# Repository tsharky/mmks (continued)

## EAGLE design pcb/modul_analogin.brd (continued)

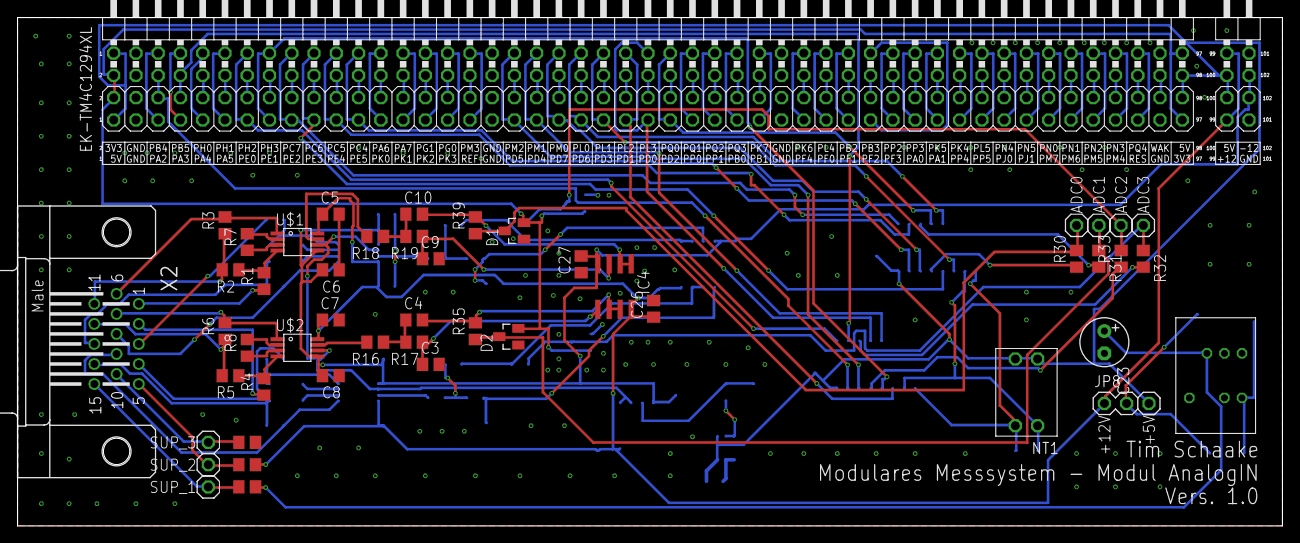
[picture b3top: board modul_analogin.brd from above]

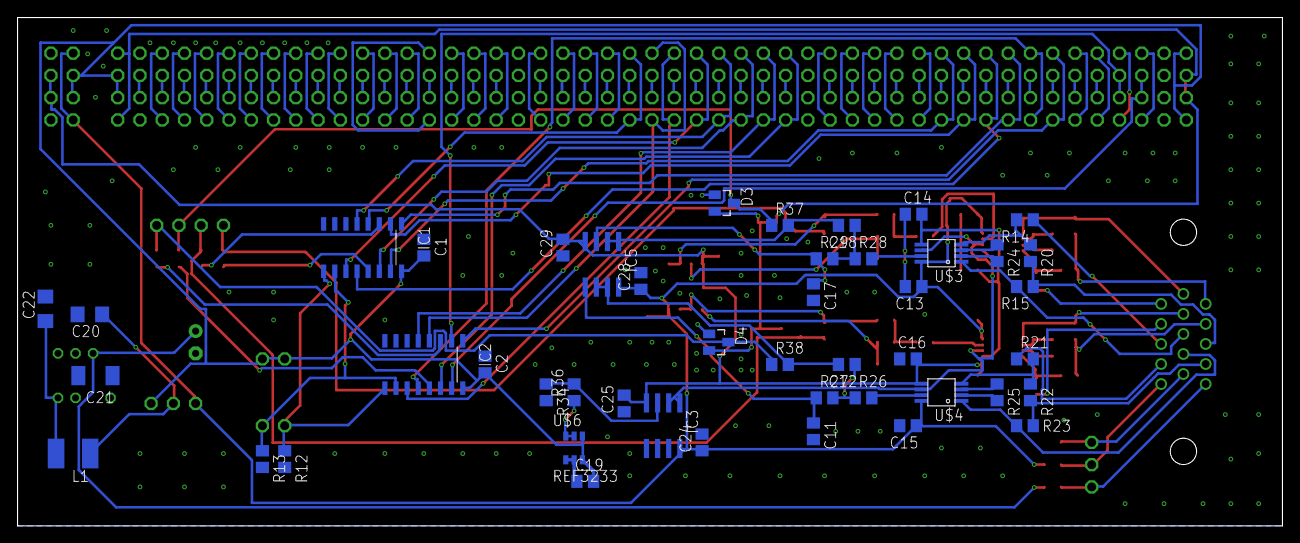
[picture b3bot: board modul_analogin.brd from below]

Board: 2 copper layers, 144.3 x 58.0 mm, 96 parts (46 on the bottom side), 153 nets.

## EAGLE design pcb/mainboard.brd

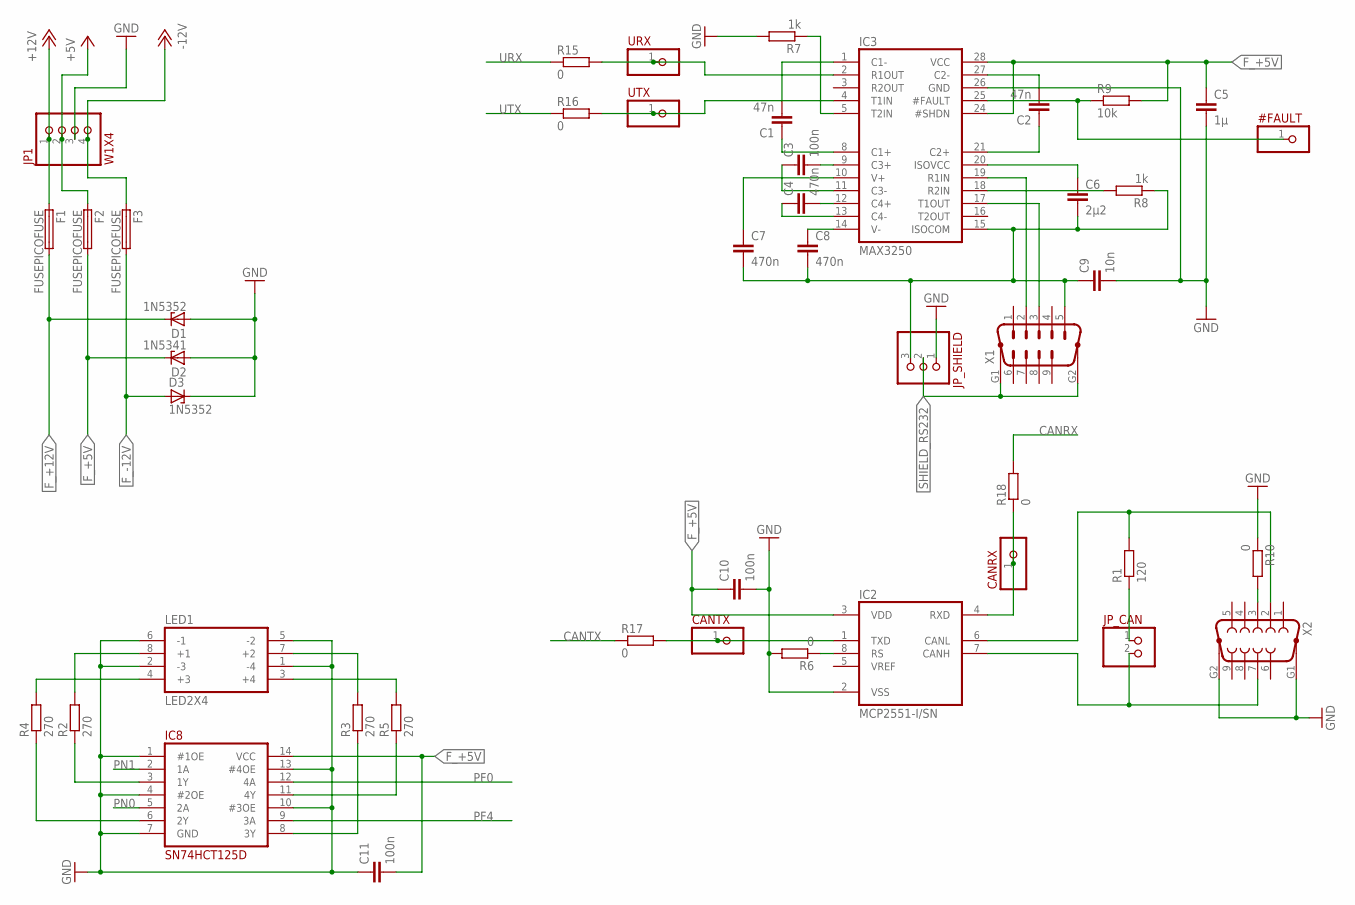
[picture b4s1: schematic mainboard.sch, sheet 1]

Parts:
#FAULT: PINH-1X1; 1X1
C1, C2: 47n; C2220
C3, C10, C11: 100n; C0805
C4, C7, C8: 470n; C0805
C5: 1µ; C0805
C6: 2µ2; C0805
C9: 10n; C1812
CANRX: PINH-1X1; 1X1
CANTX: PINH-1X1; 1X1
D1, D3: 1N5352; C1702-15
D2: 1N5341; C1702-15
F1, F2, F3: FUSEPICOFUSE; PICOFUSE
IC2: MCP2551-I/SN; SO08
IC3: MAX3250; SSOP28_A28M-3
IC8: SN74HCT125D; SOIC14_D
JP1: W1X4
JP_CAN: PINH-1X2; 1X2
JP_SHIELD: PINH-1X3; 1X3
LED1: LED2X4
R1: 120; R0805
R2, R3, R4, R5: 270; R0805
R6, R10, R15, R16, R17, R18: 0; R0805
R7, R8: 1k; R0805
R9: 10k; R0805
URX: PINH-1X1; 1X1
UTX: PINH-1X1; 1X1
X1: M09HP
X2: F09HP

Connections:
+5V: F2.1, JP1.2
+12V: F1.1, JP1.1
-12V: F3.1, JP1.4
CANRX: R18.2; also elsewhere on the board
CANTX: R17.1; also elsewhere on the board
F_+5V: C5.1, C10.1, C11.2, D2.C, F2.2, IC2.3 (VDD), IC3.24 (#SHDN), IC3.28 (VCC), IC8.14 (VCC), R9.2; also elsewhere on the board
F_+12V: D1.C, F1.2; also elsewhere on the board
F_-12V: D3.A, F3.2; also elsewhere on the board
GND: C5.2, C9.2, C10.2, C11.1, D1.A, D2.A, D3.C, IC2.2 (VSS), IC3.26 (GND), IC8.1 (#1OE), IC8.4 (#2OE), IC8.7 (GND), IC8.10 (#3OE), IC8.13 (#4OE), JP1.3, JP_SHIELD.1, LED1.1 (-4), LED1.2 (-3), LED1.5 (-2), LED1.6 (-1), R6.2, R7.2, R10.1, X2.G1, X2.G2; also elsewhere on the board
ISOCOM: C6.2, C7.2, C8.2, C9.1, IC3.15 (ISOCOM), JP_SHIELD.3, R8.1, X1.5
unnamed: JP_CAN.1, R1.1
unnamed: IC3.17 (T1OUT), X1.3
unnamed: C4.2, IC3.12 (C4+)
unnamed: C4.1, IC3.13 (C4-)
unnamed: IC3.19 (R1IN), X1.2
unnamed: C3.2, IC3.9 (C3+)
unnamed: C3.1, IC3.11 (C3-)
unnamed: C2.1, IC3.21 (C2+)
unnamed: C2.2, IC3.27 (C2-)
unnamed: C1.2, IC3.1 (C1-)
unnamed: C1.1, IC3.8 (C1+)
unnamed: C6.1, IC3.20 (ISOVCC)
unnamed: IC3.2 (R1OUT), R15.2, URX.1
unnamed: IC3.4 (T1IN), R16.2, UTX.1
unnamed: CANTX.1, IC2.1 (TXD), R17.2
unnamed: CANRX.1, IC2.4 (RXD), R18.1
unnamed: IC2.8 (RS), R6.1
unnamed: LED1.7 (+2), R3.2
unnamed: IC8.3 (1Y), R2.1
unnamed: IC8.6 (2Y), R4.1
unnamed: IC8.8 (3Y), R3.1
unnamed: IC8.11 (4Y), R5.1
unnamed: LED1.3 (+4), R5.2
unnamed: LED1.8 (+1), R2.2
unnamed: LED1.4 (+3), R4.2
unnamed: IC3.18 (R2IN), R8.2
unnamed: IC3.5 (T2IN), R7.1
unnamed: #FAULT.1, IC3.25 (#FAULT), R9.1
unnamed: R10.2, X2.3
unnamed: IC2.7 (CANH), JP_CAN.2, X2.7
unnamed: IC2.6 (CANL), R1.2, X2.2
PF0: IC8.12 (4A); also elsewhere on the board
PF4: IC8.9 (3A); also elsewhere on the board
PN0: IC8.5 (2A); also elsewhere on the board
PN1: IC8.2 (1A); also elsewhere on the board
SHIELD_RS232: JP_SHIELD.2, X1.G1, X1.G2
URX: R15.1; also elsewhere on the board
UTX: R16.1; also elsewhere on the board
V+: C7.1, IC3.10 (V+)
V-: C8.1, IC3.14 (V-)

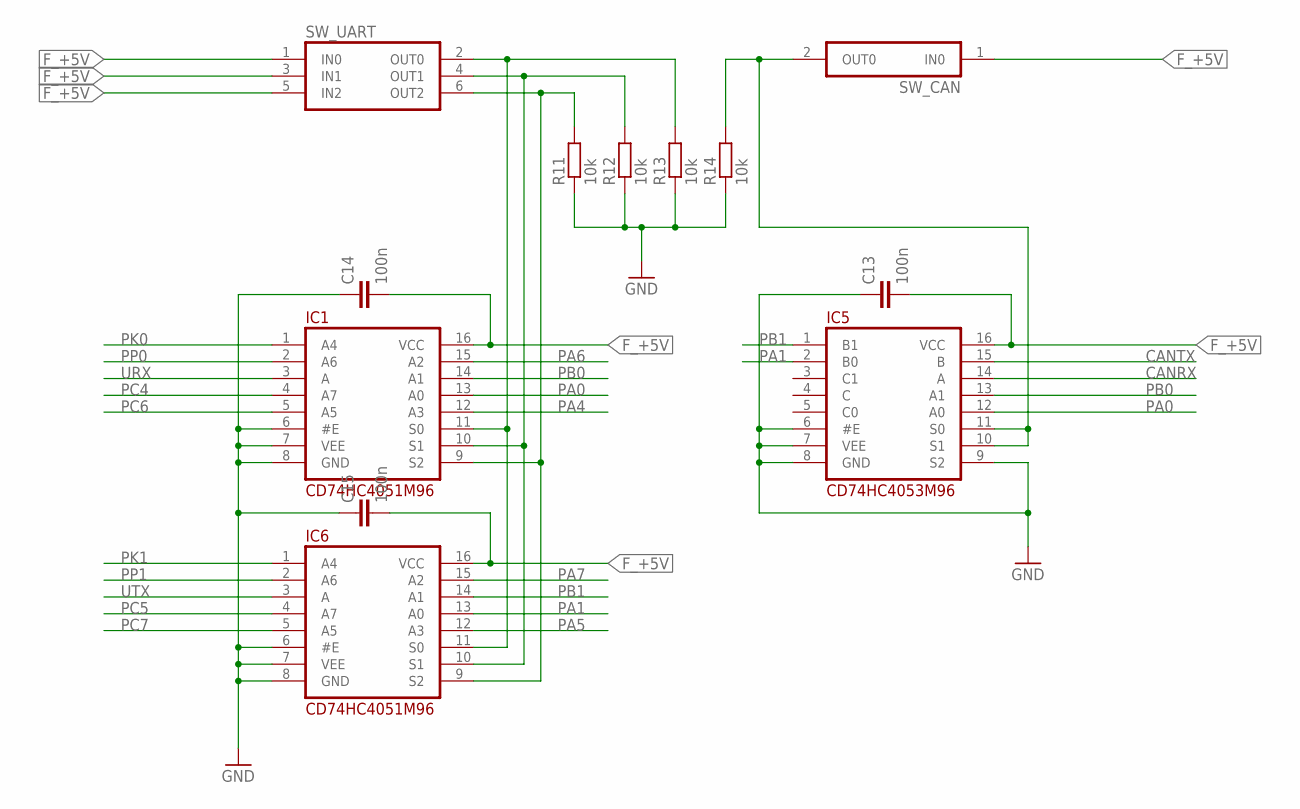
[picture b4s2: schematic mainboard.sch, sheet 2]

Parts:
C13, C14, C15: 100n; C0805
IC1, IC6: CD74HC4051M96; SOIC16_D
IC5: CD74HC4053M96; SOIC16_D
R11, R12, R13, R14: 10k; R0805
SW_CAN: NT01
SW_UART: NT03

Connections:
CANRX: IC5.14 (A); also elsewhere on the board
CANTX: IC5.15 (B); also elsewhere on the board
F_+5V: C13.2, C14.2, C15.2, IC1.16 (VCC), IC5.16 (VCC), IC6.16 (VCC), SW_CAN.1 (IN0), SW_UART.1 (IN0), SW_UART.3 (IN1), SW_UART.5 (IN2); also elsewhere on the board
GND: C13.1, C14.1, C15.1, IC1.6 (#E), IC1.7 (VEE), IC1.8 (GND), IC5.6 (#E), IC5.7 (VEE), IC5.8 (GND), IC5.9 (S2), IC6.6 (#E), IC6.7 (VEE), IC6.8 (GND), R11.1, R12.1, R13.1, R14.1; also elsewhere on the board
unnamed: IC1.9 (S2), IC6.9 (S2), R11.2, SW_UART.6 (OUT2)
unnamed: IC1.10 (S1), IC6.10 (S1), R12.2, SW_UART.4 (OUT1)
unnamed: IC1.11 (S0), IC6.11 (S0), R13.2, SW_UART.2 (OUT0)
unnamed: IC5.10 (S1), IC5.11 (S0), R14.2, SW_CAN.2 (OUT0)
PA0: IC1.13 (A0), IC5.12 (A0); also elsewhere on the board
PA1: IC5.2 (B0), IC6.13 (A0); also elsewhere on the board
PA4: IC1.12 (A3); also elsewhere on the board
PA5: IC6.12 (A3); also elsewhere on the board
PA6: IC1.15 (A2); also elsewhere on the board
PA7: IC6.15 (A2); also elsewhere on the board
PB0: IC1.14 (A1), IC5.13 (A1); also elsewhere on the board
PB1: IC5.1 (B1), IC6.14 (A1); also elsewhere on the board
PC4: IC1.4 (A7); also elsewhere on the board
PC5: IC6.4 (A7); also elsewhere on the board
PC6: IC1.5 (A5); also elsewhere on the board
PC7: IC6.5 (A5); also elsewhere on the board
PK0: IC1.1 (A4); also elsewhere on the board
PK1: IC6.1 (A4); also elsewhere on the board
PP0: IC1.2 (A6); also elsewhere on the board
PP1: IC6.2 (A6); also elsewhere on the board
URX: IC1.3 (A); also elsewhere on the board
UTX: IC6.3 (A); also elsewhere on the board

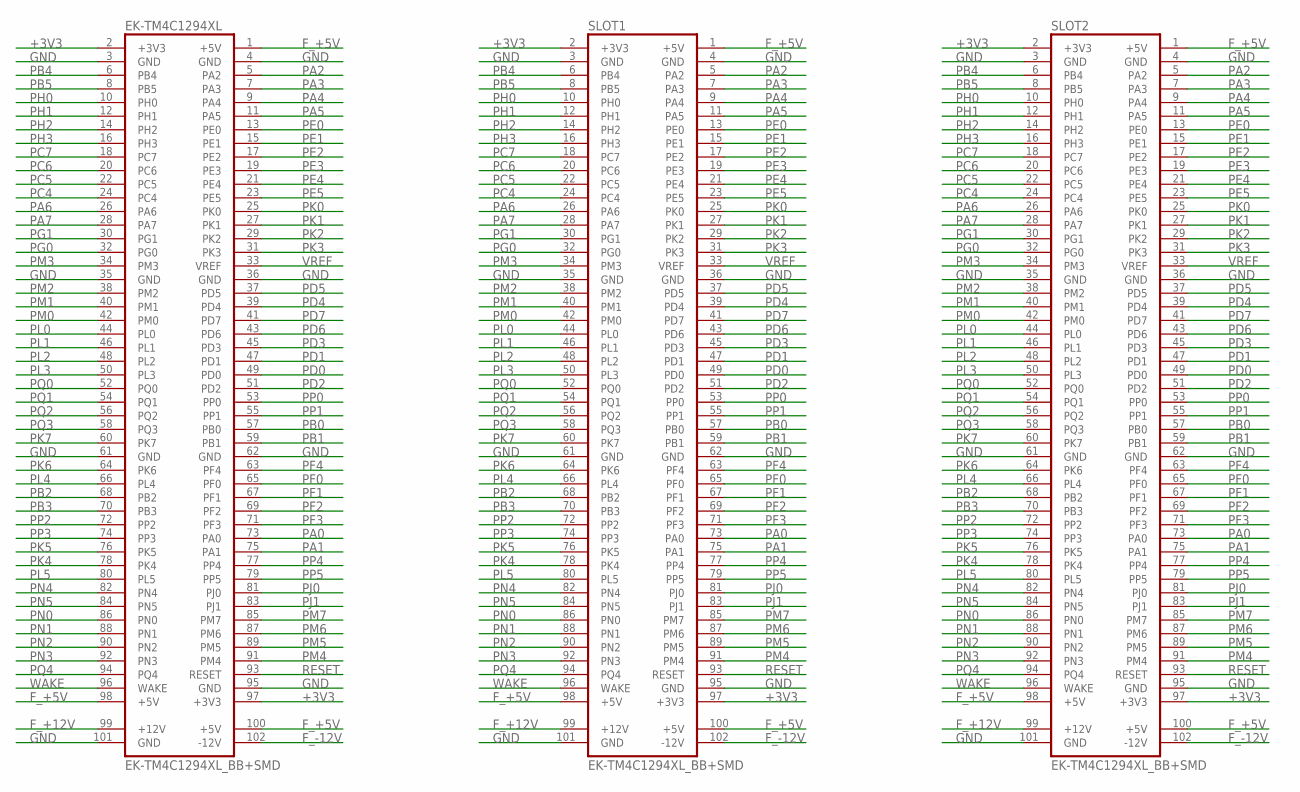
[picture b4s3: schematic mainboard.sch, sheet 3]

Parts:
EK-TM4C1294XL: EK-TM4C1294XL_BB+SMD
SLOT1, SLOT2: EK-TM4C1294XL_BB+SMD

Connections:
+3V3: EK-TM4C1294XL.2 (+3V3), EK-TM4C1294XL.97 (+3V3), SLOT1.2 (+3V3), SLOT1.97 (+3V3), SLOT2.2 (+3V3), SLOT2.97 (+3V3); also elsewhere on the board
F_+5V: EK-TM4C1294XL.1 (+5V), EK-TM4C1294XL.98 (+5V), EK-TM4C1294XL.100 (+5V), SLOT1.1 (+5V), SLOT1.98 (+5V), SLOT1.100 (+5V), SLOT2.1 (+5V), SLOT2.98 (+5V), SLOT2.100 (+5V); also elsewhere on the board
F_+12V: EK-TM4C1294XL.99 (+12V), SLOT1.99 (+12V), SLOT2.99 (+12V); also elsewhere on the board
F_-12V: EK-TM4C1294XL.102 (-12V), SLOT1.102 (-12V), SLOT2.102 (-12V); also elsewhere on the board
GND: EK-TM4C1294XL.3 (GND), EK-TM4C1294XL.4 (GND), EK-TM4C1294XL.35 (GND), EK-TM4C1294XL.36 (GND), EK-TM4C1294XL.61 (GND), EK-TM4C1294XL.62 (GND), EK-TM4C1294XL.95 (GND), EK-TM4C1294XL.101 (GND), SLOT1.3 (GND), SLOT1.4 (GND), SLOT1.35 (GND), SLOT1.36 (GND), SLOT1.61 (GND), SLOT1.62 (GND), SLOT1.95 (GND), SLOT1.101 (GND), SLOT2.3 (GND), SLOT2.4 (GND), SLOT2.35 (GND), SLOT2.36 (GND), SLOT2.61 (GND), SLOT2.62 (GND), SLOT2.95 (GND), SLOT2.101 (GND); also elsewhere on the board
PA0: EK-TM4C1294XL.73 (PA0), SLOT1.73 (PA0), SLOT2.73 (PA0); also elsewhere on the board
PA1: EK-TM4C1294XL.75 (PA1), SLOT1.75 (PA1), SLOT2.75 (PA1); also elsewhere on the board
PA2: EK-TM4C1294XL.5 (PA2), SLOT1.5 (PA2), SLOT2.5 (PA2); also elsewhere on the board
PA3: EK-TM4C1294XL.7 (PA3), SLOT1.7 (PA3), SLOT2.7 (PA3); also elsewhere on the board
PA4: EK-TM4C1294XL.9 (PA4), SLOT1.9 (PA4), SLOT2.9 (PA4); also elsewhere on the board
PA5: EK-TM4C1294XL.11 (PA5), SLOT1.11 (PA5), SLOT2.11 (PA5); also elsewhere on the board
PA6: EK-TM4C1294XL.26 (PA6), SLOT1.26 (PA6), SLOT2.26 (PA6); also elsewhere on the board
PA7: EK-TM4C1294XL.28 (PA7), SLOT1.28 (PA7), SLOT2.28 (PA7); also elsewhere on the board
PB0: EK-TM4C1294XL.57 (PB0), SLOT1.57 (PB0), SLOT2.57 (PB0); also elsewhere on the board
PB1: EK-TM4C1294XL.59 (PB1), SLOT1.59 (PB1), SLOT2.59 (PB1); also elsewhere on the board
PB2: EK-TM4C1294XL.68 (PB2), SLOT1.68 (PB2), SLOT2.68 (PB2); also elsewhere on the board
PB3: EK-TM4C1294XL.70 (PB3), SLOT1.70 (PB3), SLOT2.70 (PB3); also elsewhere on the board
PB4: EK-TM4C1294XL.6 (PB4), SLOT1.6 (PB4), SLOT2.6 (PB4); also elsewhere on the board
PB5: EK-TM4C1294XL.8 (PB5), SLOT1.8 (PB5), SLOT2.8 (PB5); also elsewhere on the board
PC4: EK-TM4C1294XL.24 (PC4), SLOT1.24 (PC4), SLOT2.24 (PC4); also elsewhere on the board
PC5: EK-TM4C1294XL.22 (PC5), SLOT1.22 (PC5), SLOT2.22 (PC5); also elsewhere on the board
PC6: EK-TM4C1294XL.20 (PC6), SLOT1.20 (PC6), SLOT2.20 (PC6); also elsewhere on the board
PC7: EK-TM4C1294XL.18 (PC7), SLOT1.18 (PC7), SLOT2.18 (PC7); also elsewhere on the board
PD0: EK-TM4C1294XL.49 (PD0), SLOT1.49 (PD0), SLOT2.49 (PD0); also elsewhere on the board
PD1: EK-TM4C1294XL.47 (PD1), SLOT1.47 (PD1), SLOT2.47 (PD1); also elsewhere on the board
PD2: EK-TM4C1294XL.51 (PD2), SLOT1.51 (PD2), SLOT2.51 (PD2); also elsewhere on the board
PD3: EK-TM4C1294XL.45 (PD3), SLOT1.45 (PD3), SLOT2.45 (PD3); also elsewhere on the board
PD4: EK-TM4C1294XL.39 (PD4), SLOT1.39 (PD4), SLOT2.39 (PD4); also elsewhere on the board
PD5: EK-TM4C1294XL.37 (PD5), SLOT1.37 (PD5), SLOT2.37 (PD5); also elsewhere on the board
PD6: EK-TM4C1294XL.43 (PD6), SLOT1.43 (PD6), SLOT2.43 (PD6); also elsewhere on the board
PD7: EK-TM4C1294XL.41 (PD7), SLOT1.41 (PD7), SLOT2.41 (PD7); also elsewhere on the board
PE0: EK-TM4C1294XL.13 (PE0), SLOT1.13 (PE0), SLOT2.13 (PE0); also elsewhere on the board
PE1: EK-TM4C1294XL.15 (PE1), SLOT1.15 (PE1), SLOT2.15 (PE1); also elsewhere on the board
PE2: EK-TM4C1294XL.17 (PE2), SLOT1.17 (PE2), SLOT2.17 (PE2); also elsewhere on the board
PE3: EK-TM4C1294XL.19 (PE3), SLOT1.19 (PE3), SLOT2.19 (PE3); also elsewhere on the board
PE4: EK-TM4C1294XL.21 (PE4), SLOT1.21 (PE4), SLOT2.21 (PE4); also elsewhere on the board
PE5: EK-TM4C1294XL.23 (PE5), SLOT1.23 (PE5), SLOT2.23 (PE5); also elsewhere on the board
PF0: EK-TM4C1294XL.65 (PF0), SLOT1.65 (PF0), SLOT2.65 (PF0); also elsewhere on the board
PF1: EK-TM4C1294XL.67 (PF1), SLOT1.67 (PF1), SLOT2.67 (PF1); also elsewhere on the board
PF2: EK-TM4C1294XL.69 (PF2), SLOT1.69 (PF2), SLOT2.69 (PF2); also elsewhere on the board
PF3: EK-TM4C1294XL.71 (PF3), SLOT1.71 (PF3), SLOT2.71 (PF3); also elsewhere on the board
PF4: EK-TM4C1294XL.63 (PF4), SLOT1.63 (PF4), SLOT2.63 (PF4); also elsewhere on the board
PG0: EK-TM4C1294XL.32 (PG0), SLOT1.32 (PG0), SLOT2.32 (PG0); also elsewhere on the board
PG1: EK-TM4C1294XL.30 (PG1), SLOT1.30 (PG1), SLOT2.30 (PG1); also elsewhere on the board
PH0: EK-TM4C1294XL.10 (PH0), SLOT1.10 (PH0), SLOT2.10 (PH0); also elsewhere on the board
PH1: EK-TM4C1294XL.12 (PH1), SLOT1.12 (PH1), SLOT2.12 (PH1); also elsewhere on the board
PH2: EK-TM4C1294XL.14 (PH2), SLOT1.14 (PH2), SLOT2.14 (PH2); also elsewhere on the board
PH3: EK-TM4C1294XL.16 (PH3), SLOT1.16 (PH3), SLOT2.16 (PH3); also elsewhere on the board
PJ0: EK-TM4C1294XL.81 (PJ0), SLOT1.81 (PJ0), SLOT2.81 (PJ0); also elsewhere on the board
PJ1: EK-TM4C1294XL.83 (PJ1), SLOT1.83 (PJ1), SLOT2.83 (PJ1); also elsewhere on the board
PK0: EK-TM4C1294XL.25 (PK0), SLOT1.25 (PK0), SLOT2.25 (PK0); also elsewhere on the board
PK1: EK-TM4C1294XL.27 (PK1), SLOT1.27 (PK1), SLOT2.27 (PK1); also elsewhere on the board
PK2: EK-TM4C1294XL.29 (PK2), SLOT1.29 (PK2), SLOT2.29 (PK2); also elsewhere on the board
PK3: EK-TM4C1294XL.31 (PK3), SLOT1.31 (PK3), SLOT2.31 (PK3); also elsewhere on the board
PK4: EK-TM4C1294XL.78 (PK4), SLOT1.78 (PK4), SLOT2.78 (PK4); also elsewhere on the board
PK5: EK-TM4C1294XL.76 (PK5), SLOT1.76 (PK5), SLOT2.76 (PK5); also elsewhere on the board
PK6: EK-TM4C1294XL.64 (PK6), SLOT1.64 (PK6), SLOT2.64 (PK6); also elsewhere on the board
PK7: EK-TM4C1294XL.60 (PK7), SLOT1.60 (PK7), SLOT2.60 (PK7); also elsewhere on the board
PL0: EK-TM4C1294XL.44 (PL0), SLOT1.44 (PL0), SLOT2.44 (PL0); also elsewhere on the board
PL1: EK-TM4C1294XL.46 (PL1), SLOT1.46 (PL1), SLOT2.46 (PL1); also elsewhere on the board
PL2: EK-TM4C1294XL.48 (PL2), SLOT1.48 (PL2), SLOT2.48 (PL2); also elsewhere on the board
PL3: EK-TM4C1294XL.50 (PL3), SLOT1.50 (PL3), SLOT2.50 (PL3); also elsewhere on the board
PL4: EK-TM4C1294XL.66 (PL4), SLOT1.66 (PL4), SLOT2.66 (PL4); also elsewhere on the board
PL5: EK-TM4C1294XL.80 (PL5), SLOT1.80 (PL5), SLOT2.80 (PL5); also elsewhere on the board
PM0: EK-TM4C1294XL.42 (PM0), SLOT1.42 (PM0), SLOT2.42 (PM0); also elsewhere on the board
PM1: EK-TM4C1294XL.40 (PM1), SLOT1.40 (PM1), SLOT2.40 (PM1); also elsewhere on the board
PM2: EK-TM4C1294XL.38 (PM2), SLOT1.38 (PM2), SLOT2.38 (PM2); also elsewhere on the board
PM3: EK-TM4C1294XL.34 (PM3), SLOT1.34 (PM3), SLOT2.34 (PM3); also elsewhere on the board
PM4: EK-TM4C1294XL.91 (PM4), SLOT1.91 (PM4), SLOT2.91 (PM4); also elsewhere on the board
PM5: EK-TM4C1294XL.89 (PM5), SLOT1.89 (PM5), SLOT2.89 (PM5); also elsewhere on the board
PM6: EK-TM4C1294XL.87 (PM6), SLOT1.87 (PM6), SLOT2.87 (PM6); also elsewhere on the board
PM7: EK-TM4C1294XL.85 (PM7), SLOT1.85 (PM7), SLOT2.85 (PM7); also elsewhere on the board
PN0: EK-TM4C1294XL.86 (PN0), SLOT1.86 (PN0), SLOT2.86 (PN0); also elsewhere on the board
PN1: EK-TM4C1294XL.88 (PN1), SLOT1.88 (PN1), SLOT2.88 (PN1); also elsewhere on the board
PN2: EK-TM4C1294XL.90 (PN2), SLOT1.90 (PN2), SLOT2.90 (PN2); also elsewhere on the board
PN3: EK-TM4C1294XL.92 (PN3), SLOT1.92 (PN3), SLOT2.92 (PN3); also elsewhere on the board
PN4: EK-TM4C1294XL.82 (PN4), SLOT1.82 (PN4), SLOT2.82 (PN4); also elsewhere on the board
PN5: EK-TM4C1294XL.84 (PN5), SLOT1.84 (PN5), SLOT2.84 (PN5); also elsewhere on the board
PP0: EK-TM4C1294XL.53 (PP0), SLOT1.53 (PP0), SLOT2.53 (PP0); also elsewhere on the board
PP1: EK-TM4C1294XL.55 (PP1), SLOT1.55 (PP1), SLOT2.55 (PP1); also elsewhere on the board
PP2: EK-TM4C1294XL.72 (PP2), SLOT1.72 (PP2), SLOT2.72 (PP2); also elsewhere on the board
PP3: EK-TM4C1294XL.74 (PP3), SLOT1.74 (PP3), SLOT2.74 (PP3); also elsewhere on the board
PP4: EK-TM4C1294XL.77 (PP4), SLOT1.77 (PP4), SLOT2.77 (PP4); also elsewhere on the board
PP5: EK-TM4C1294XL.79 (PP5), SLOT1.79 (PP5), SLOT2.79 (PP5); also elsewhere on the board
PQ0: EK-TM4C1294XL.52 (PQ0), SLOT1.52 (PQ0), SLOT2.52 (PQ0); also elsewhere on the board
PQ1: EK-TM4C1294XL.54 (PQ1), SLOT1.54 (PQ1), SLOT2.54 (PQ1); also elsewhere on the board
PQ2: EK-TM4C1294XL.56 (PQ2), SLOT1.56 (PQ2), SLOT2.56 (PQ2); also elsewhere on the board
PQ3: EK-TM4C1294XL.58 (PQ3), SLOT1.58 (PQ3), SLOT2.58 (PQ3); also elsewhere on the board
PQ4: EK-TM4C1294XL.94 (PQ4), SLOT1.94 (PQ4), SLOT2.94 (PQ4); also elsewhere on the board
RESET: EK-TM4C1294XL.93 (RESET), SLOT1.93 (RESET), SLOT2.93 (RESET); also elsewhere on the board
VREF: EK-TM4C1294XL.33 (VREF), SLOT1.33 (VREF), SLOT2.33 (VREF); also elsewhere on the board
WAKE: EK-TM4C1294XL.96 (WAKE), SLOT1.96 (WAKE), SLOT2.96 (WAKE); also elsewhere on the board

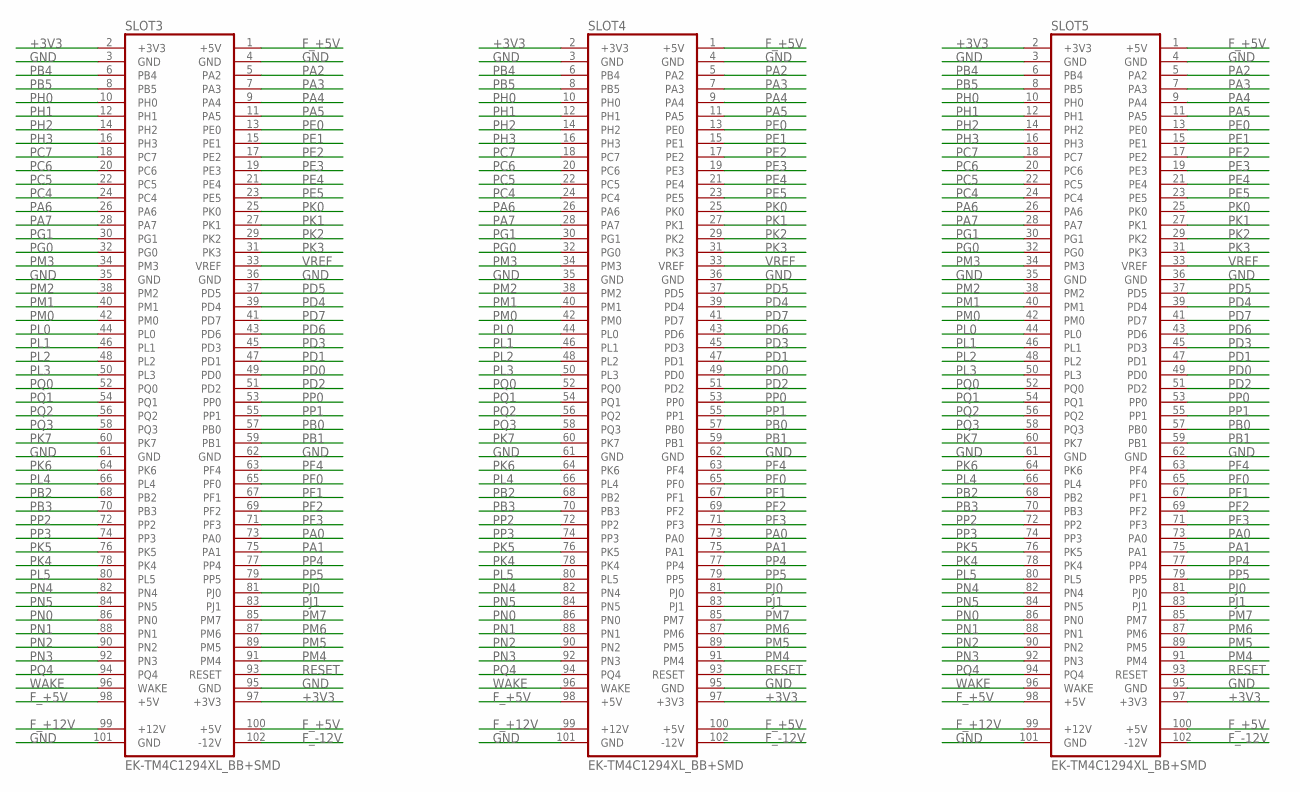
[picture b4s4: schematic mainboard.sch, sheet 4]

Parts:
SLOT3, SLOT4, SLOT5: EK-TM4C1294XL_BB+SMD

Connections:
+3V3: SLOT3.2 (+3V3), SLOT3.97 (+3V3), SLOT4.2 (+3V3), SLOT4.97 (+3V3), SLOT5.2 (+3V3), SLOT5.97 (+3V3); also elsewhere on the board
F_+5V: SLOT3.1 (+5V), SLOT3.98 (+5V), SLOT3.100 (+5V), SLOT4.1 (+5V), SLOT4.98 (+5V), SLOT4.100 (+5V), SLOT5.1 (+5V), SLOT5.98 (+5V), SLOT5.100 (+5V); also elsewhere on the board
F_+12V: SLOT3.99 (+12V), SLOT4.99 (+12V), SLOT5.99 (+12V); also elsewhere on the board
F_-12V: SLOT3.102 (-12V), SLOT4.102 (-12V), SLOT5.102 (-12V); also elsewhere on the board
GND: SLOT3.3 (GND), SLOT3.4 (GND), SLOT3.35 (GND), SLOT3.36 (GND), SLOT3.61 (GND), SLOT3.62 (GND), SLOT3.95 (GND), SLOT3.101 (GND), SLOT4.3 (GND), SLOT4.4 (GND), SLOT4.35 (GND), SLOT4.36 (GND), SLOT4.61 (GND), SLOT4.62 (GND), SLOT4.95 (GND), SLOT4.101 (GND), SLOT5.3 (GND), SLOT5.4 (GND), SLOT5.35 (GND), SLOT5.36 (GND), SLOT5.61 (GND), SLOT5.62 (GND), SLOT5.95 (GND), SLOT5.101 (GND); also elsewhere on the board
PA0: SLOT3.73 (PA0), SLOT4.73 (PA0), SLOT5.73 (PA0); also elsewhere on the board
PA1: SLOT3.75 (PA1), SLOT4.75 (PA1), SLOT5.75 (PA1); also elsewhere on the board
PA2: SLOT3.5 (PA2), SLOT4.5 (PA2), SLOT5.5 (PA2); also elsewhere on the board
PA3: SLOT3.7 (PA3), SLOT4.7 (PA3), SLOT5.7 (PA3); also elsewhere on the board
PA4: SLOT3.9 (PA4), SLOT4.9 (PA4), SLOT5.9 (PA4); also elsewhere on the board
PA5: SLOT3.11 (PA5), SLOT4.11 (PA5), SLOT5.11 (PA5); also elsewhere on the board
PA6: SLOT3.26 (PA6), SLOT4.26 (PA6), SLOT5.26 (PA6); also elsewhere on the board
PA7: SLOT3.28 (PA7), SLOT4.28 (PA7), SLOT5.28 (PA7); also elsewhere on the board
PB0: SLOT3.57 (PB0), SLOT4.57 (PB0), SLOT5.57 (PB0); also elsewhere on the board
PB1: SLOT3.59 (PB1), SLOT4.59 (PB1), SLOT5.59 (PB1); also elsewhere on the board
PB2: SLOT3.68 (PB2), SLOT4.68 (PB2), SLOT5.68 (PB2); also elsewhere on the board
PB3: SLOT3.70 (PB3), SLOT4.70 (PB3), SLOT5.70 (PB3); also elsewhere on the board
PB4: SLOT3.6 (PB4), SLOT4.6 (PB4), SLOT5.6 (PB4); also elsewhere on the board
PB5: SLOT3.8 (PB5), SLOT4.8 (PB5), SLOT5.8 (PB5); also elsewhere on the board
PC4: SLOT3.24 (PC4), SLOT4.24 (PC4), SLOT5.24 (PC4); also elsewhere on the board
PC5: SLOT3.22 (PC5), SLOT4.22 (PC5), SLOT5.22 (PC5); also elsewhere on the board
PC6: SLOT3.20 (PC6), SLOT4.20 (PC6), SLOT5.20 (PC6); also elsewhere on the board
PC7: SLOT3.18 (PC7), SLOT4.18 (PC7), SLOT5.18 (PC7); also elsewhere on the board
PD0: SLOT3.49 (PD0), SLOT4.49 (PD0), SLOT5.49 (PD0); also elsewhere on the board
PD1: SLOT3.47 (PD1), SLOT4.47 (PD1), SLOT5.47 (PD1); also elsewhere on the board
PD2: SLOT3.51 (PD2), SLOT4.51 (PD2), SLOT5.51 (PD2); also elsewhere on the board
PD3: SLOT3.45 (PD3), SLOT4.45 (PD3), SLOT5.45 (PD3); also elsewhere on the board
PD4: SLOT3.39 (PD4), SLOT4.39 (PD4), SLOT5.39 (PD4); also elsewhere on the board
PD5: SLOT3.37 (PD5), SLOT4.37 (PD5), SLOT5.37 (PD5); also elsewhere on the board
PD6: SLOT3.43 (PD6), SLOT4.43 (PD6), SLOT5.43 (PD6); also elsewhere on the board
PD7: SLOT3.41 (PD7), SLOT4.41 (PD7), SLOT5.41 (PD7); also elsewhere on the board
PE0: SLOT3.13 (PE0), SLOT4.13 (PE0), SLOT5.13 (PE0); also elsewhere on the board
PE1: SLOT3.15 (PE1), SLOT4.15 (PE1), SLOT5.15 (PE1); also elsewhere on the board
PE2: SLOT3.17 (PE2), SLOT4.17 (PE2), SLOT5.17 (PE2); also elsewhere on the board
PE3: SLOT3.19 (PE3), SLOT4.19 (PE3), SLOT5.19 (PE3); also elsewhere on the board
PE4: SLOT3.21 (PE4), SLOT4.21 (PE4), SLOT5.21 (PE4); also elsewhere on the board
PE5: SLOT3.23 (PE5), SLOT4.23 (PE5), SLOT5.23 (PE5); also elsewhere on the board
PF0: SLOT3.65 (PF0), SLOT4.65 (PF0), SLOT5.65 (PF0); also elsewhere on the board
PF1: SLOT3.67 (PF1), SLOT4.67 (PF1), SLOT5.67 (PF1); also elsewhere on the board
PF2: SLOT3.69 (PF2), SLOT4.69 (PF2), SLOT5.69 (PF2); also elsewhere on the board
PF3: SLOT3.71 (PF3), SLOT4.71 (PF3), SLOT5.71 (PF3); also elsewhere on the board
PF4: SLOT3.63 (PF4), SLOT4.63 (PF4), SLOT5.63 (PF4); also elsewhere on the board
PG0: SLOT3.32 (PG0), SLOT4.32 (PG0), SLOT5.32 (PG0); also elsewhere on the board
PG1: SLOT3.30 (PG1), SLOT4.30 (PG1), SLOT5.30 (PG1); also elsewhere on the board
PH0: SLOT3.10 (PH0), SLOT4.10 (PH0), SLOT5.10 (PH0); also elsewhere on the board
PH1: SLOT3.12 (PH1), SLOT4.12 (PH1), SLOT5.12 (PH1); also elsewhere on the board
PH2: SLOT3.14 (PH2), SLOT4.14 (PH2), SLOT5.14 (PH2); also elsewhere on the board
PH3: SLOT3.16 (PH3), SLOT4.16 (PH3), SLOT5.16 (PH3); also elsewhere on the board
PJ0: SLOT3.81 (PJ0), SLOT4.81 (PJ0), SLOT5.81 (PJ0); also elsewhere on the board
PJ1: SLOT3.83 (PJ1), SLOT4.83 (PJ1), SLOT5.83 (PJ1); also elsewhere on the board
PK0: SLOT3.25 (PK0), SLOT4.25 (PK0), SLOT5.25 (PK0); also elsewhere on the board
PK1: SLOT3.27 (PK1), SLOT4.27 (PK1), SLOT5.27 (PK1); also elsewhere on the board
PK2: SLOT3.29 (PK2), SLOT4.29 (PK2), SLOT5.29 (PK2); also elsewhere on the board
PK3: SLOT3.31 (PK3), SLOT4.31 (PK3), SLOT5.31 (PK3); also elsewhere on the board
PK4: SLOT3.78 (PK4), SLOT4.78 (PK4), SLOT5.78 (PK4); also elsewhere on the board
PK5: SLOT3.76 (PK5), SLOT4.76 (PK5), SLOT5.76 (PK5); also elsewhere on the board
PK6: SLOT3.64 (PK6), SLOT4.64 (PK6), SLOT5.64 (PK6); also elsewhere on the board
PK7: SLOT3.60 (PK7), SLOT4.60 (PK7), SLOT5.60 (PK7); also elsewhere on the board
PL0: SLOT3.44 (PL0), SLOT4.44 (PL0), SLOT5.44 (PL0); also elsewhere on the board
PL1: SLOT3.46 (PL1), SLOT4.46 (PL1), SLOT5.46 (PL1); also elsewhere on the board
PL2: SLOT3.48 (PL2), SLOT4.48 (PL2), SLOT5.48 (PL2); also elsewhere on the board
PL3: SLOT3.50 (PL3), SLOT4.50 (PL3), SLOT5.50 (PL3); also elsewhere on the board
PL4: SLOT3.66 (PL4), SLOT4.66 (PL4), SLOT5.66 (PL4); also elsewhere on the board
PL5: SLOT3.80 (PL5), SLOT4.80 (PL5), SLOT5.80 (PL5); also elsewhere on the board
PM0: SLOT3.42 (PM0), SLOT4.42 (PM0), SLOT5.42 (PM0); also elsewhere on the board
PM1: SLOT3.40 (PM1), SLOT4.40 (PM1), SLOT5.40 (PM1); also elsewhere on the board
PM2: SLOT3.38 (PM2), SLOT4.38 (PM2), SLOT5.38 (PM2); also elsewhere on the board
PM3: SLOT3.34 (PM3), SLOT4.34 (PM3), SLOT5.34 (PM3); also elsewhere on the board
PM4: SLOT3.91 (PM4), SLOT4.91 (PM4), SLOT5.91 (PM4); also elsewhere on the board
PM5: SLOT3.89 (PM5), SLOT4.89 (PM5), SLOT5.89 (PM5); also elsewhere on the board
PM6: SLOT3.87 (PM6), SLOT4.87 (PM6), SLOT5.87 (PM6); also elsewhere on the board
PM7: SLOT3.85 (PM7), SLOT4.85 (PM7), SLOT5.85 (PM7); also elsewhere on the board
PN0: SLOT3.86 (PN0), SLOT4.86 (PN0), SLOT5.86 (PN0); also elsewhere on the board
PN1: SLOT3.88 (PN1), SLOT4.88 (PN1), SLOT5.88 (PN1); also elsewhere on the board
PN2: SLOT3.90 (PN2), SLOT4.90 (PN2), SLOT5.90 (PN2); also elsewhere on the board
PN3: SLOT3.92 (PN3), SLOT4.92 (PN3), SLOT5.92 (PN3); also elsewhere on the board
PN4: SLOT3.82 (PN4), SLOT4.82 (PN4), SLOT5.82 (PN4); also elsewhere on the board
PN5: SLOT3.84 (PN5), SLOT4.84 (PN5), SLOT5.84 (PN5); also elsewhere on the board
PP0: SLOT3.53 (PP0), SLOT4.53 (PP0), SLOT5.53 (PP0); also elsewhere on the board
PP1: SLOT3.55 (PP1), SLOT4.55 (PP1), SLOT5.55 (PP1); also elsewhere on the board
PP2: SLOT3.72 (PP2), SLOT4.72 (PP2), SLOT5.72 (PP2); also elsewhere on the board
PP3: SLOT3.74 (PP3), SLOT4.74 (PP3), SLOT5.74 (PP3); also elsewhere on the board
PP4: SLOT3.77 (PP4), SLOT4.77 (PP4), SLOT5.77 (PP4); also elsewhere on the board
PP5: SLOT3.79 (PP5), SLOT4.79 (PP5), SLOT5.79 (PP5); also elsewhere on the board
PQ0: SLOT3.52 (PQ0), SLOT4.52 (PQ0), SLOT5.52 (PQ0); also elsewhere on the board
PQ1: SLOT3.54 (PQ1), SLOT4.54 (PQ1), SLOT5.54 (PQ1); also elsewhere on the board
PQ2: SLOT3.56 (PQ2), SLOT4.56 (PQ2), SLOT5.56 (PQ2); also elsewhere on the board
PQ3: SLOT3.58 (PQ3), SLOT4.58 (PQ3), SLOT5.58 (PQ3); also elsewhere on the board
PQ4: SLOT3.94 (PQ4), SLOT4.94 (PQ4), SLOT5.94 (PQ4); also elsewhere on the board
RESET: SLOT3.93 (RESET), SLOT4.93 (RESET), SLOT5.93 (RESET); also elsewhere on the board
VREF: SLOT3.33 (VREF), SLOT4.33 (VREF), SLOT5.33 (VREF); also elsewhere on the board
WAKE: SLOT3.96 (WAKE), SLOT4.96 (WAKE), SLOT5.96 (WAKE); also elsewhere on the board
